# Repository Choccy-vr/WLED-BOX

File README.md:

# WLED-BOX
An easy, compact WLED controller. Powered with USB-C for easy connection and enclosed in a nice, organized small box.

I made this because most WLED Controllers out there are very overkill for most home users' use cases or way too expensive. 
This WLED Controller provides an easy and simple way to control your WLED Lights while giving you a nice, clean, and smooth experience.
## Images

### PCB

### CAD

## BOM

|Item                                   |,Quanity                                                                                                                                                                                                                                                                                                                                                                                                                                              |,Source|,Price|,Total|FIELD6|
|---------------------------------------|------------------------------------------------------------------------------------------------------------------------------------------------------------------------------------------------------------------------------------------------------------------------------------------------------------------------------------------------------------------------------------------------------------------------------------------------------|-------|------|------|------|
|M2 Screws,1(50pcs),https               |//www.aliexpress.us/item/3256805084387535.html?spm=a2g0o.cart.0.0.2a4238datfbJZ4&mp=1&pdp_npi=5%40dis%21USD%21USD%201.12%21USD%201.12%21%21USD%200.31%21%21%21%40210337bc17504290038523905ef430%2112000032432141682%21ct%21US%213108417632%21%211%210&_gl=1*1enbcc0*_gcl_au*NDM2NDExMDYwLjE3NDk1NzAxOTM.*_ga*MTI2OTU4ODg1MTA3NjI0MC4xNzUwMzc4MzE5NjA1*_ga_VED1YSGNC7*czE3NTA0Mjc4MTckbzIkZzEkdDE3NTA0MjkwMDUkajckbDAkaDA.&gatewayAdapt=glo2usa,$1.12 ,|       |      |      |      |
|M2 Heat Set Inserts,1(50pcs),https     |//www.aliexpress.us/item/3256803396040989.html?spm=a2g0o.cart.0.0.2a4238datfbJZ4&mp=1&pdp_npi=5%40dis%21USD%21USD%201.88%21USD%201.64%21%21USD%201.61%21%21%21%40210337bc17504290038523905ef430%2112000026370649721%21ct%21US%213108417632%21%211%210&_gl=1*1enbcc0*_gcl_au*NDM2NDExMDYwLjE3NDk1NzAxOTM.*_ga*MTI2OTU4ODg1MTA3NjI0MC4xNzUwMzc4MzE5NjA1*_ga_VED1YSGNC7*czE3NTA0Mjc4MTckbzIkZzEkdDE3NTA0MjkwMDUkajckbDAkaDA.&gatewayAdapt=glo2usa,$1.64 ,|       |      |      |      |
|JST-SM  3pins,1(10pairs),https         |//www.aliexpress.us/item/3256804429301946.html?spm=a2g0o.cart.0.0.2a4238datfbJZ4&mp=1&pdp_npi=5%40dis%21USD%21USD%203.18%21USD%203.18%21%21USD%200.93%21%21%21%40210337bc17504290038523905ef430%2112000029927782269%21ct%21US%213108417632%21%211%210&_gl=1*1enbcc0*_gcl_au*NDM2NDExMDYwLjE3NDk1NzAxOTM.*_ga*MTI2OTU4ODg1MTA3NjI0MC4xNzUwMzc4MzE5NjA1*_ga_VED1YSGNC7*czE3NTA0Mjc4MTckbzIkZzEkdDE3NTA0MjkwMDUkajckbDAkaDA.&gatewayAdapt=glo2usa,$3.18 ,|       |      |      |      |
|XIAO ESP 32 C3,1,https                 |//www.seeedstudio.com/Seeed-XIAO-ESP32C3-p-5431.html,$4.90 ,                                                                                                                                                                                                                                                                                                                                                                                          |       |      |      |      |
|USB C,3,https                          |//www.digikey.com/en/products/detail/gct/USB4135-GF-A/16036137,$2.01 ,                                                                                                                                                                                                                                                                                                                                                                                |       |      |      |      |
|PCB,1,https                            |//cart.jlcpcb.com/shopcart/cart/,$2.10 ,                                                                                                                                                                                                                                                                                                                                                                                                              |       |      |      |      |
|,,,,$30.32 (Includes Shipping and Taxes)|                                                                                                                                                                                                                                                                                                                                                                                                                                                      |       |      |      |      |

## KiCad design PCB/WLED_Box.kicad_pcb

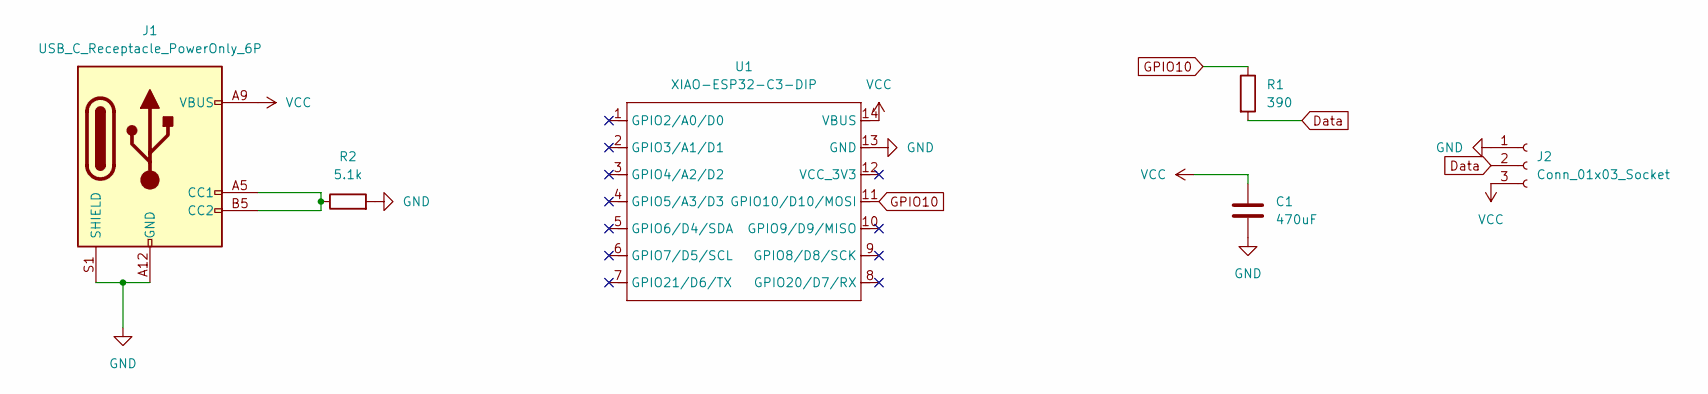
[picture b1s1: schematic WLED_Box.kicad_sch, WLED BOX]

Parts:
C1: 470uF; CP_Radial_D10.0mm_P5.00mm
J1: USB_C_Receptacle_PowerOnly_6P; USB_C_Receptacle_GCT_USB4135-GF-A_6P_TopMnt_Horizontal
J2: Conn_01x03_Socket; PinHeader_1x03_P2.54mm_Vertical
R1: 390; R_Axial_DIN0207_L6.3mm_D2.5mm_P7.62mm_Horizontal
R2: 5.1k; R_Axial_DIN0207_L6.3mm_D2.5mm_P7.62mm_Horizontal
U1: XIAO-ESP32-C3-DIP; XIAO-ESP32C3-DIP

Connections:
Data: J2.2, R1.2
GND: C1.2, J1.A12 (GND), J1.B12 (GND), J1.S1 (SHIELD), J2.1, R2.2, U1.13 (GND)
GPIO10: R1.1, U1.11 (GPIO10/D10/MOSI)
unnamed: J1.A5 (CC1), J1.B5 (CC2), R2.1
VCC: C1.1, J1.A9 (VBUS), J1.B9 (VBUS), J2.3, U1.14 (VBUS)

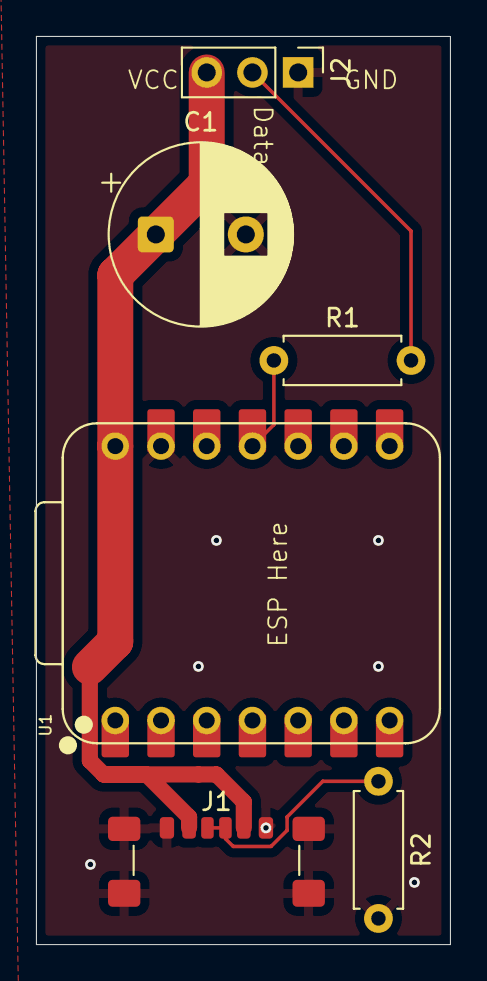
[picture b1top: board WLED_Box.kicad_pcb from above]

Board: 2 copper layers, 23.0 x 50.5 mm, 6 parts (0 on the bottom side), 5 nets.

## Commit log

2025-06-20 CAD Finishing
